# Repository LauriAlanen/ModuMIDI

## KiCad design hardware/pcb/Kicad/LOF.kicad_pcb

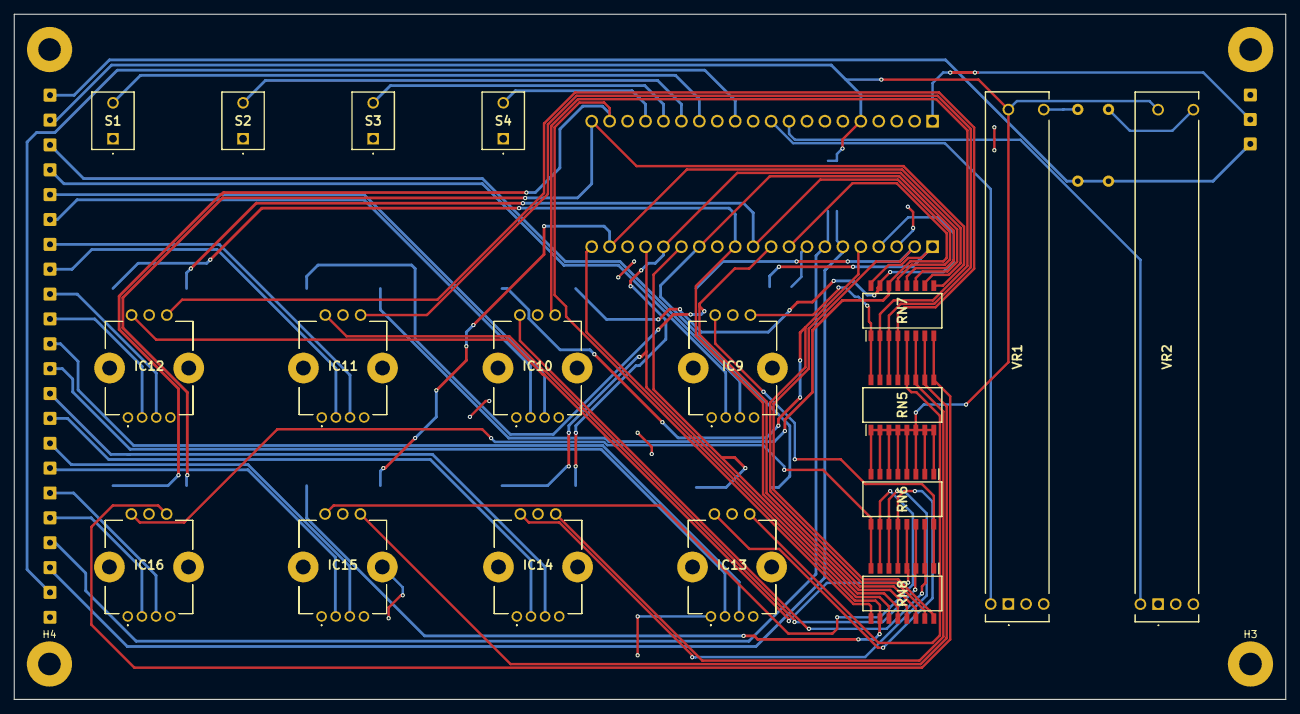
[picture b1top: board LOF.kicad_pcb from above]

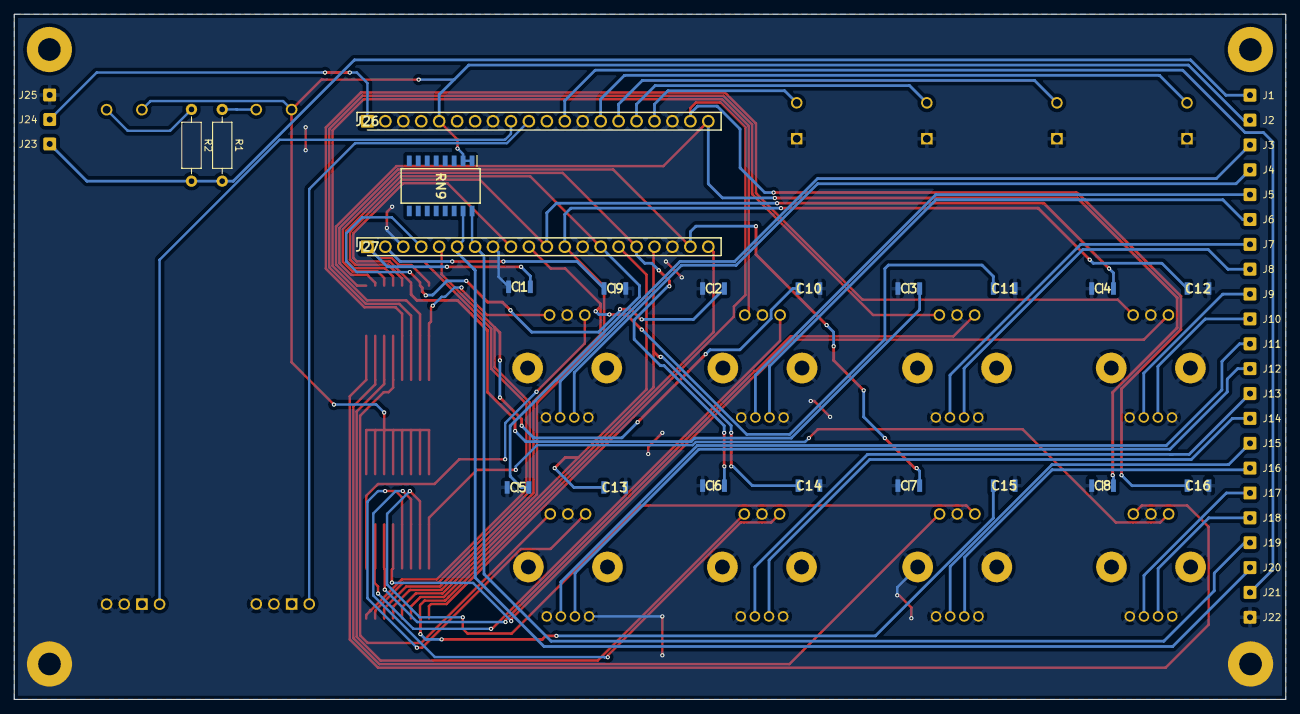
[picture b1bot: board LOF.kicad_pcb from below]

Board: 4 copper layers, 180.0 x 97.0 mm, 68 parts (46 on the bottom side), 63 nets.

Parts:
C1, C2, C3, C4, C5, C6, C7, C8, C9, C10, C11, C12, C13, C14, C15, C16: 885012208009; CAPC3216X90N
H1, H2, H3, H4: MountingHole; MountingHole_3.2mm_M3_Pad
IC9, IC10, IC11, IC12, IC13, IC14, IC15, IC16: PEL12D-4225S-S1024; PEL12D4225SS1024
J1, J2, J3, J4, J5, J6, J7, J8, J9, J10, J11, J12, J13, J14, J15, J16, J17, J18, J19, J20, J21, J22, J23, J24, J25: Conn_01x01; SolderWire-0.25sqmm_1x01_D0.65mm_OD1.7mm
J26, J27: M20-7822046; RHDR20W70P0X254_1X20_5120X250X865P
R1, R2: R; R_Axial_DIN0207_L6.3mm_D2.5mm_P10.16mm_Horizontal
RN5, RN6, RN7, RN8, RN9: 4816P-T01-103LF; SOIC127P762X215-16N
S1, S2, S3, S4: 2MS6T1B3M2QES
VR1, VR2: PTL60-15O1-104B2; PTL6015O1104B2

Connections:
/3V3: J2.1, J26.5, RN5.1, RN5.2, RN5.3, RN5.4, RN5.5, RN5.6, RN5.7, RN5.8, RN6.1, RN6.2, RN6.3, RN6.4, RN6.5, RN6.6, RN6.7, RN6.8, RN9.1, RN9.2, VR1.3 (CW), VR2.3 (CW)
/A_Out1: C1.1, J27.1, RN7.16
/A_Out2: C2.1, J27.4, RN7.15
/A_Out3: C3.1, J27.9, RN7.14
/A_Out4: C4.1, J27.11, RN7.13
/A_Out5: C5.1, J27.14, RN7.12
/A_Out6: C6.1, J27.16, RN7.11
/A_Out7: C7.1, J27.19, RN7.10
/A_Out8: C8.1, J26.20, RN7.9
/B_Out1: C9.1, J27.2, RN8.16
/B_Out2: C10.1, J27.5, RN8.15
/B_Out3: C11.1, J27.10, RN8.14
/B_Out4: C12.1, J27.12, RN8.13
/B_Out5: C13.1, J27.15, RN8.12
/B_Out6: C14.1, J27.17, RN8.11
/B_Out7: C15.1, J27.20, RN8.10
/B_Out8: C16.1, J26.19, RN8.9
/GPIO18: J26.17, S4.3 (NC)
/GPIO19: J26.16, S3.3 (NC)
/GPIO20: J26.15, S2.3 (NC)
/GPIO21: J26.14, S1.3 (NC)
/LED_VCC: J1.1, J23.1, R1.2, R2.2
/OE: J21.1, J26.12
/PWM_0: IC9.3 (+_2), J3.1
/PWM_1: IC9.2 (+_1), J4.1
/PWM_2: IC10.3 (+_2), J5.1
/PWM_3: IC10.2 (+_1), J6.1
/PWM_4: IC11.3 (+_2), J7.1
/PWM_5: IC11.2 (+_1), J8.1
/PWM_6: IC12.3 (+_2), J9.1
/PWM_7: IC12.2 (+_1), J10.1
/PWM_8: IC13.3 (+_2), J11.1
/PWM_9: IC13.2 (+_1), J12.1
/PWM_10: IC14.3 (+_2), J13.1
/PWM_11: IC14.2 (+_1), J14.1
/PWM_12: IC15.3 (+_2), J15.1
/PWM_13: IC15.2 (+_1), J16.1
/PWM_14: IC16.3 (+_2), J17.1
/PWM_15: IC16.2 (+_1), J18.1
/RC Filtered Encoders/encoders1/AIn1: IC9.A1 (CCW), RN5.16, RN7.1
/RC Filtered Encoders/encoders1/AIn2: IC10.A1 (CCW), RN5.15, RN7.2
/RC Filtered Encoders/encoders1/AIn3: IC11.A1 (CCW), RN5.14, RN7.3
/RC Filtered Encoders/encoders1/AIn4: IC12.A1 (CCW), RN5.13, RN7.4
/RC Filtered Encoders/encoders1/AIn5: IC13.A1 (CCW), RN5.12, RN7.5
/RC Filtered Encoders/encoders1/AIn6: IC14.A1 (CCW), RN5.11, RN7.6
/RC Filtered Encoders/encoders1/AIn7: IC15.A1 (CCW), RN5.10, RN7.7
/RC Filtered Encoders/encoders1/AIn8: IC16.A1 (CCW), RN5.9, RN7.8
/RC Filtered Encoders/encoders1/BIn1: IC9.B1 (CW), RN6.16, RN8.1
/RC Filtered Encoders/encoders1/BIn2: IC10.B1 (CW), RN6.15, RN8.2
/RC Filtered Encoders/encoders1/BIn3: IC11.B1 (CW), RN6.14, RN8.3
/RC Filtered Encoders/encoders1/BIn4: IC12.B1 (CW), RN6.13, RN8.4
/RC Filtered Encoders/encoders1/BIn5: IC13.B1 (CW), RN6.12, RN8.5
/RC Filtered Encoders/encoders1/BIn6: IC14.B1 (CW), RN6.11, RN8.6
/RC Filtered Encoders/encoders1/BIn7: IC15.B1 (CW), RN6.10, RN8.7
/RC Filtered Encoders/encoders1/BIn8: IC16.B1 (CW), RN6.9, RN8.8
/SCL: J19.1, J27.7, RN9.16
/SDA: J20.1, J27.6, RN9.15
/VBUS: J24.1, J26.1
/WIPER_VR1: J26.10, VR1.2 (WIPER)
/WIPER_VR2: J26.9, VR2.2 (WIPER)
GND: C1.2, C2.2, C3.2, C4.2, C5.2, C6.2, C7.2, C8.2, C9.2, C10.2, C11.2, C12.2, C13.2, C14.2, C15.2, C16.2, IC9.1 (-), IC9.4 (COM), IC9.C1 (WIPER), IC9.MH1, IC9.MH2, IC10.1 (-), IC10.4 (COM), IC10.C1 (WIPER), IC10.MH1, IC10.MH2, IC11.1 (-), IC11.4 (COM), IC11.C1 (WIPER), IC11.MH1, IC11.MH2, IC12.1 (-), IC12.4 (COM), IC12.C1 (WIPER), IC12.MH1, IC12.MH2, IC13.1 (-), IC13.4 (COM), IC13.C1 (WIPER), IC13.MH1, IC13.MH2, IC14.1 (-), IC14.4 (COM), IC14.C1 (WIPER), IC14.MH1, IC14.MH2, IC15.1 (-), IC15.4 (COM), IC15.C1 (WIPER), IC15.MH1, IC15.MH2, IC16.1 (-), IC16.4 (COM), IC16.C1 (WIPER), IC16.MH1, IC16.MH2, J22.1, J25.1, J26.3, J26.8, J26.13, J26.18, J27.3, J27.8, J27.13, J27.18, S1.1 (NO), S2.1 (NO), S3.1 (NO), S4.1 (NO), VR1.1 (CCW), VR1.E1 (E_(-)), VR1.L1 (DUMMY_TERMINAL), VR2.1 (CCW), VR2.E1 (E_(-)), VR2.L1 (DUMMY_TERMINAL)
unnamed: R1.1, VR1.B1 (B_(+))
unnamed: R2.1, VR2.B1 (B_(+))

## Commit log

2025-04-27 Added basic schema
2025-04-27 Added rest of the encoder terminal to hierarchical sheets
2025-04-27 Added variable resistor and switches
2025-04-28 Update schematic
2025-04-28 Made fixes according to the erc
2025-05-01 All components and footprints set
2025-05-04 PCB Ready
2025-05-14 Initialize project layout
2025-05-15 Add rpi pico pinout pdf
2025-05-15 Added working MIDI example
2025-05-15 Add clang formatting rules
2025-05-15 Modularize midi functions
2025-05-15 Update main to use modularized midi functions
2025-05-15 Rename modumidi to main
2025-05-15 Add logic for reading switch state and sending over midi
2025-05-15 Add logic for reading encoders and sending data over midi
2025-05-15 Limit the encoder values to 0..127
2025-05-15 Send midi values only on change
2025-05-15 Remove useless code
2025-05-15 Add switch channel validation
2025-05-15 rename encoder_id_t to encoder_ch_t
2025-05-15 Add midi input draining
2025-05-15 Start working on pca9675 driver
2025-05-15 Update comment
2025-05-17 Change MIDI channel
2025-05-17 Removed unusused last_cc variable
2025-05-17 Rework pca9685 code, now it works correctly for controlling encoders leds
2025-05-17 Add basic sweep test for pca9685, used for debugging
2025-05-17 Add pca9685_test.c
2025-05-17 Add second encoder
2025-05-29 Add logic for delta updating, and make clear comments
2025-05-29 Change main logic to utilize midi mapping struct. Change polling logic.
2025-05-29 Add midi mapping struct
2025-05-29 Add better error handling, and modularize the used functions.
2025-05-29 Change the device name
